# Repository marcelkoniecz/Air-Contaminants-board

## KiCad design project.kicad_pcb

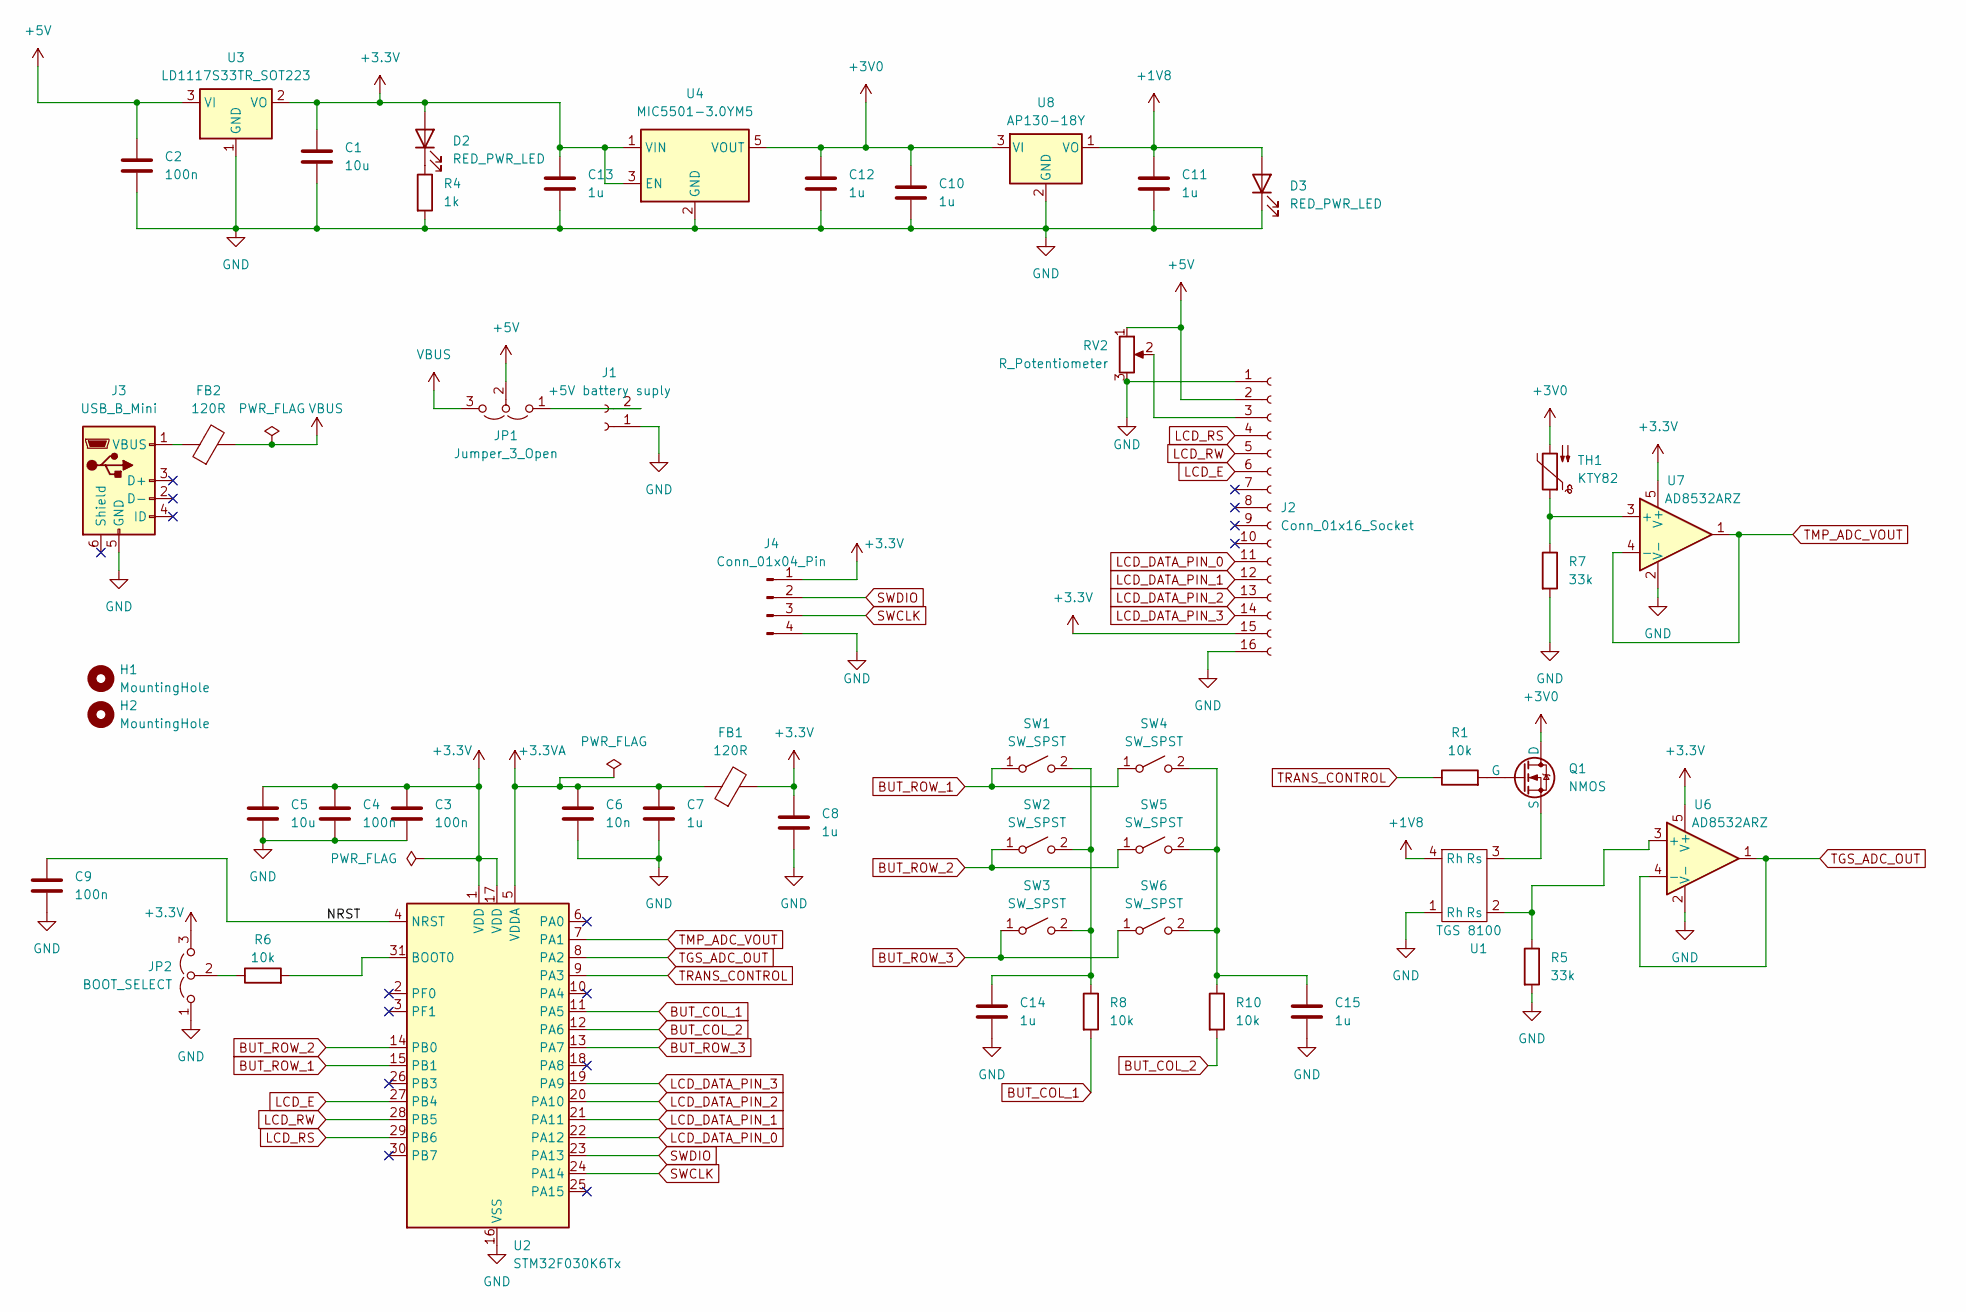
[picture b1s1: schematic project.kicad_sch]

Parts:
C1, C5: 10u; C_0603_1608Metric
C2, C3, C4, C9: 100n; C_0402_1005Metric
C6: 10n; C_0402_1005Metric
C7, C8, C10, C11, C12, C13, C14, C15: 1u; C_0402_1005Metric
D2, D3: RED_PWR_LED; LED_0805_2012Metric
FB1, FB2: 120R; L_0603_1608Metric
H1, H2: MountingHole; MountingHole_2.2mm_M2
J1: +5V battery suply; AMASS_XT30U-F_1x02_P5.0mm_Vertical
J2: Conn_01x16_Socket; PinSocket_1x16_P2.54mm_Vertical
J3: USB_B_Mini; USB_Micro-B_Wuerth_629105150521
J4: Conn_01x04_Pin; PinHeader_1x04_P2.54mm_Vertical
JP1: Jumper_3_Open; PinHeader_1x03_P1.27mm_Vertical
JP2: BOOT_SELECT; PinHeader_1x03_P1.27mm_Vertical
Q1: NMOS; TSOT-23
R1, R6, R8, R10: 10k; R_0402_1005Metric
R4: 1k; R_0402_1005Metric
R5, R7: 33k; R_0402_1005Metric
RV2: R_Potentiometer; Potentiometer_ACP_CA6-VSMD_Vertical
SW1, SW2, SW3, SW4, SW5, SW6: SW_SPST; SW_PUSH_6mm
TH1: KTY82; SOT-23
U1: TGS 8100
U2: STM32F030K6Tx; LQFP-32_7x7mm_P0.8mm
U3: LD1117S33TR_SOT223; SOT-223-3_TabPin2
U4: MIC5501-3.0YM5; SOT-23-5
U6, U7: AD8532ARZ; TSOT-23-5
U8: AP130-18Y; SOT-89-3

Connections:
+1V8: C11.1, D3.2 (A), U1.4 (Rh), U8.1 (VO)
+3.3V: C1.1, C3.1, C4.1, C5.1, C8.1, C13.1, D2.2 (A), FB1.2, J2.15, J4.1, JP2.3 (B), U2.1 (VDD), U2.17 (VDD), U3.2 (VO), U4.1 (VIN), U4.3 (EN), U6.5 (V+), U7.5 (V+)
+3.3VA: C6.1, C7.1, FB1.1, U2.5 (VDDA)
+3V0: C10.1, C12.1, Q1.1 (D), TH1.2, U4.5 (VOUT), U8.3 (VI)
+5V: C2.1, J2.2, JP1.2 (C), RV2.1, U3.3 (VI)
/NRST: C9.1, U2.4 (NRST)
BUT_COL_1: R8.2, U2.11 (PA5)
BUT_COL_2: R10.2, U2.12 (PA6)
BUT_ROW_1: SW1.1 (A), SW4.1 (A), U2.15 (PB1)
BUT_ROW_2: SW2.1 (A), SW5.1 (A), U2.14 (PB0)
BUT_ROW_3: SW3.1 (A), SW6.1 (A), U2.13 (PA7)
GND: C1.2, C2.2, C3.2, C4.2, C5.2, C6.2, C7.2, C8.2, C9.2, C10.2, C11.2, C12.2, C13.2, C14.2, C15.2, D3.1 (K), J1.1, J2.1, J2.16, J3.5 (GND), J4.4, JP2.1 (A), R4.2, R5.2, R7.2, RV2.3, U1.1 (Rh), U2.16 (VSS), U2.32 (VSS), U3.1 (GND), U4.2 (GND), U6.2 (V-), U7.2 (V-), U8.2 (GND)
LCD_DATA_PIN_0: J2.11, U2.22 (PA12)
LCD_DATA_PIN_1: J2.12, U2.21 (PA11)
LCD_DATA_PIN_2: J2.13, U2.20 (PA10)
LCD_DATA_PIN_3: J2.14, U2.19 (PA9)
LCD_E: J2.6, U2.27 (PB4)
LCD_RS: J2.4, U2.29 (PB6)
LCD_RW: J2.5, U2.28 (PB5)
unnamed: D2.1 (K), R4.1
unnamed: J1.2, JP1.1 (A)
unnamed: J2.3, RV2.2
unnamed: FB2.1, J3.1 (VBUS)
unnamed: JP2.2 (C), R6.1
unnamed: Q1.2 (G), R1.2
unnamed: Q1.3 (S), U1.3 (Rs)
unnamed: C14.1, R8.1, SW1.2 (B), SW2.2 (B), SW3.2 (B)
unnamed: C15.1, R10.1, SW4.2 (B), SW5.2 (B), SW6.2 (B)
unnamed: R6.2, U2.31 (BOOT0)
unnamed: R5.1, U1.2 (Rs), U6.3 (+)
unnamed: R7.1, TH1.1, U7.3 (+)
SWCLK: J4.3, U2.24 (PA14)
SWDIO: J4.2, U2.23 (PA13)
TGS_ADC_OUT: U2.8 (PA2), U6.1, U6.4 (-)
TMP_ADC_VOUT: U2.7 (PA1), U7.1, U7.4 (-)
TRANS_CONTROL: R1.1, U2.9 (PA3)
VBUS: FB2.2, JP1.3 (B)

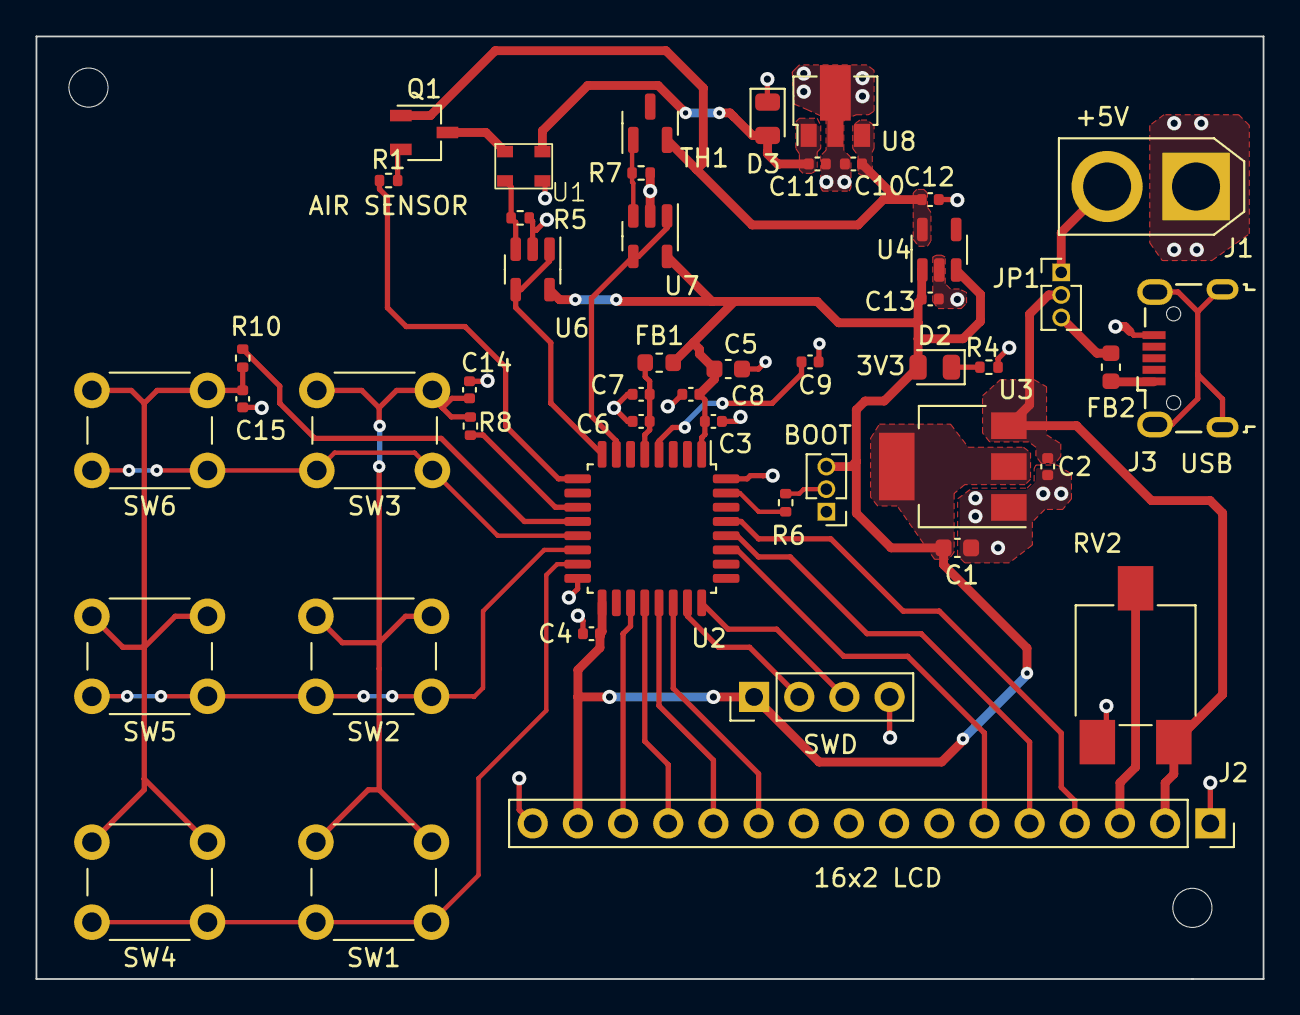
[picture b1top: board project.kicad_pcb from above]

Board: 2 copper layers, 69.0 x 53.0 mm, 50 parts (0 on the bottom side), 37 nets.

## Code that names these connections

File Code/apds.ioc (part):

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Mcu.Name=STM32F030K6Tx
Mcu.Package=LQFP32
Mcu.UserName=STM32F030K6Tx
PA1.Mode=IN1
PA1.Signal=ADC_IN1
PA11.Signal=GPIO_Output
PA13.Mode=Serial_Wire
PA13.Signal=SYS_SWDIO
PA14.Mode=Serial_Wire
PA14.Signal=SYS_SWCLK
PA2.Mode=IN2
PA2.Signal=ADC_IN2
PA5.GPIOParameters=GPIO_Label
PA5.GPIO_Label=GAS_Sensor_switch
PA5.Signal=GPIO_Output
RCC.SYSCLKFreq_VALUE=48000000
RCC.SYSCLKSource=RCC_SYSCLKSOURCE_PLLCLK
board=custom

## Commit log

2024-03-01 KiCad files
2024-03-01 Create example
2024-03-01 KiCad
2024-03-01 png schematics
2024-03-01 Create code file
2024-03-01 Added cmake-build-debug
2024-03-01 added-cmake-build-debug-remote
2024-03-01 Create Code folder
2024-03-01 Add STM32 Code
2024-03-01 Added Debug
2024-03-01 Created presentation folder
2024-03-01 Rename APDS_project_v2 (1).pdf to Project_presentation.pdf
